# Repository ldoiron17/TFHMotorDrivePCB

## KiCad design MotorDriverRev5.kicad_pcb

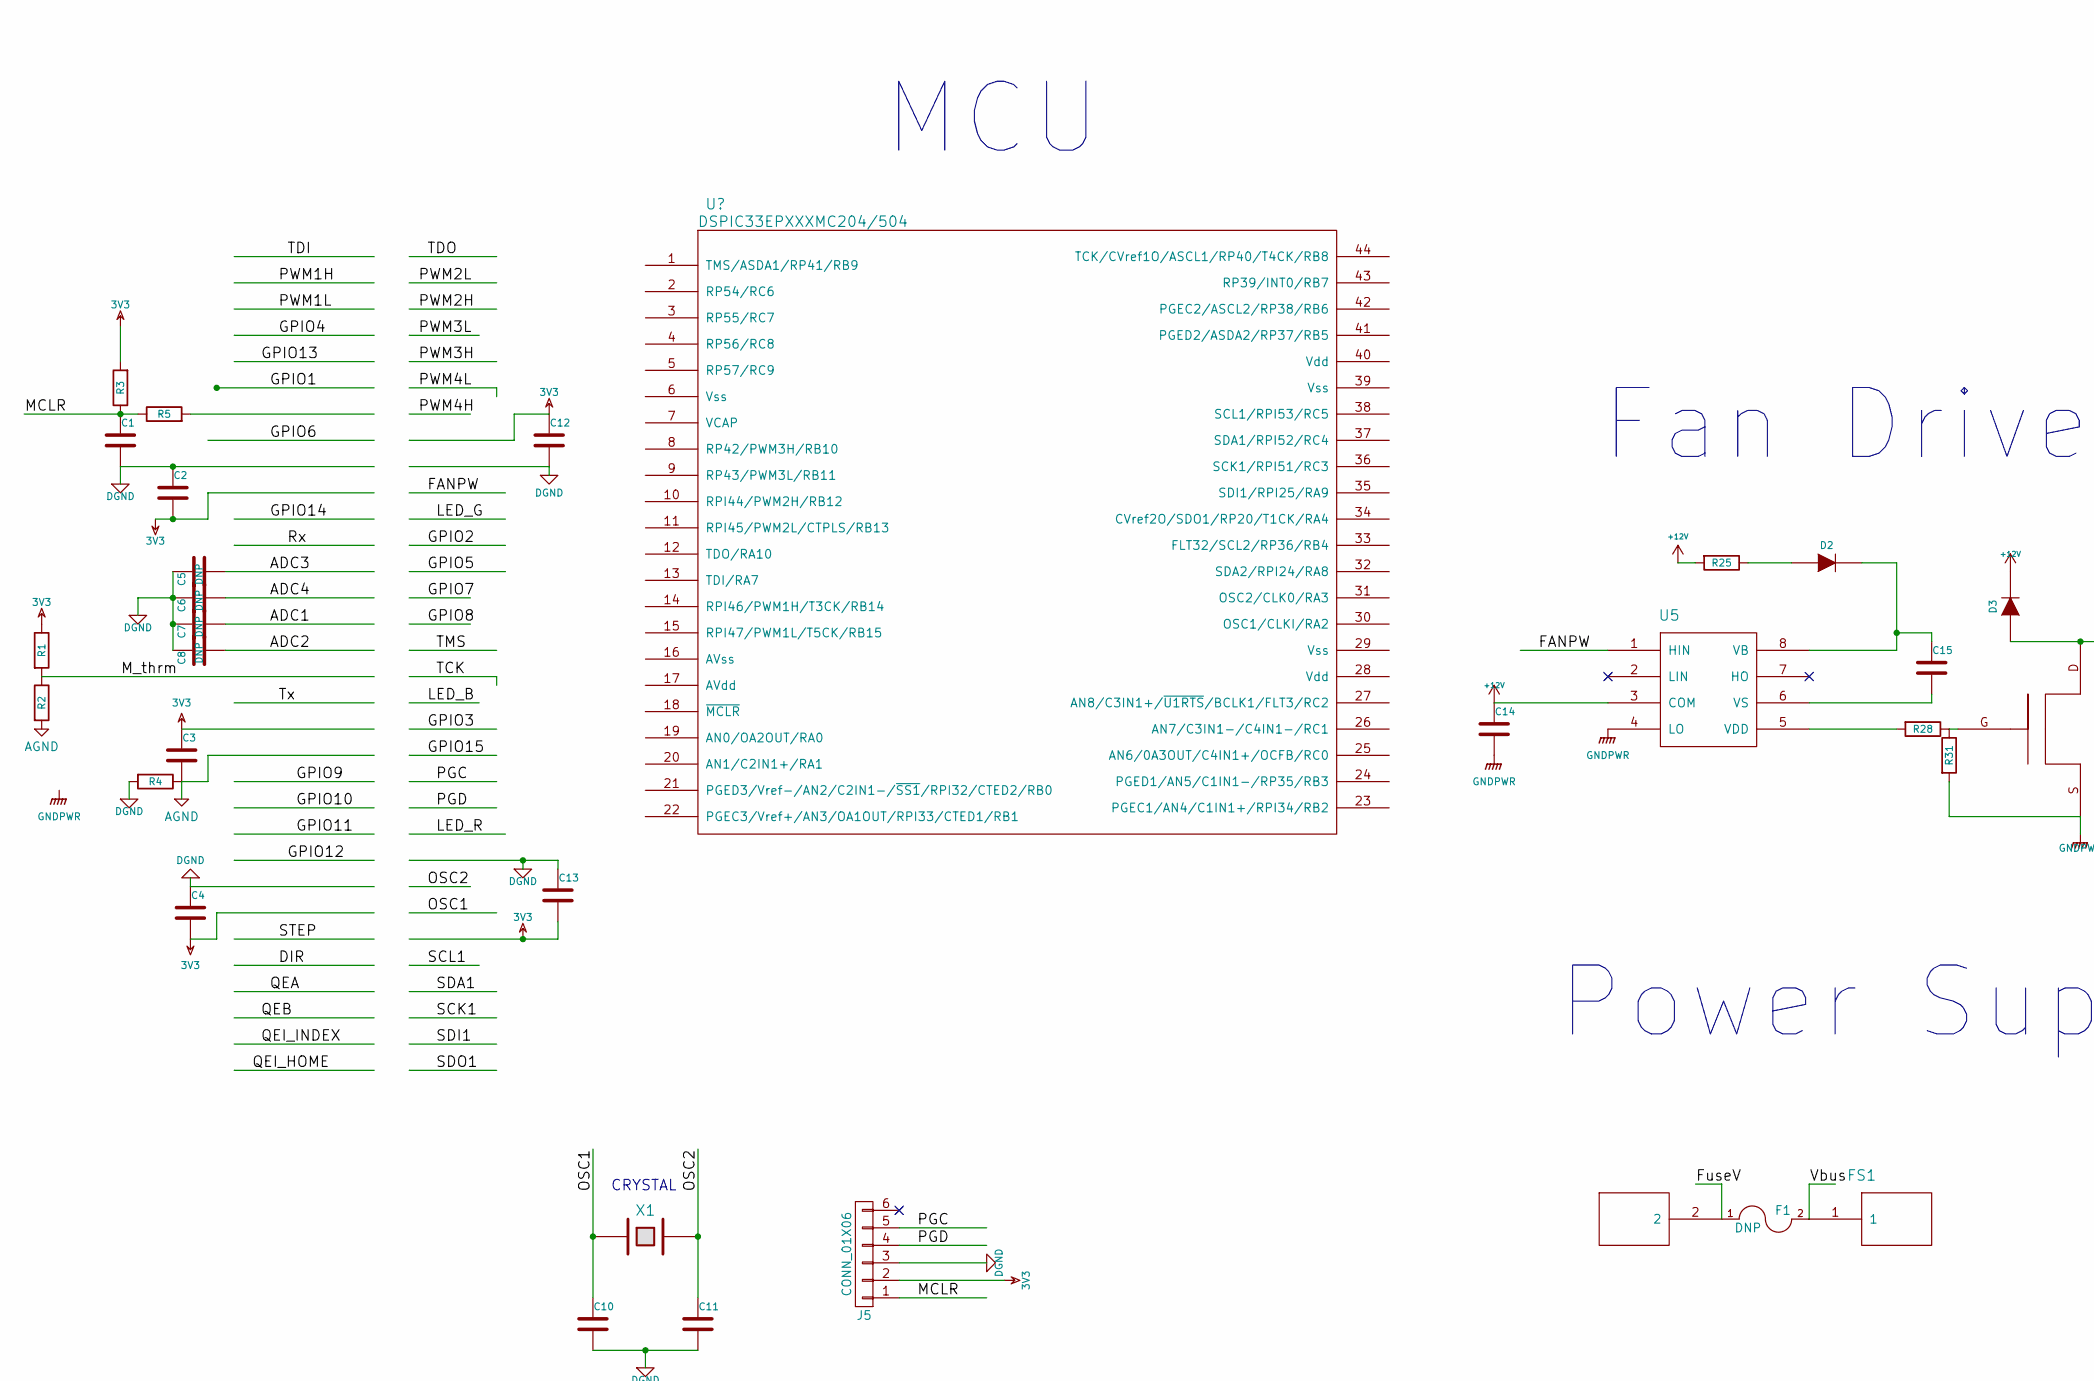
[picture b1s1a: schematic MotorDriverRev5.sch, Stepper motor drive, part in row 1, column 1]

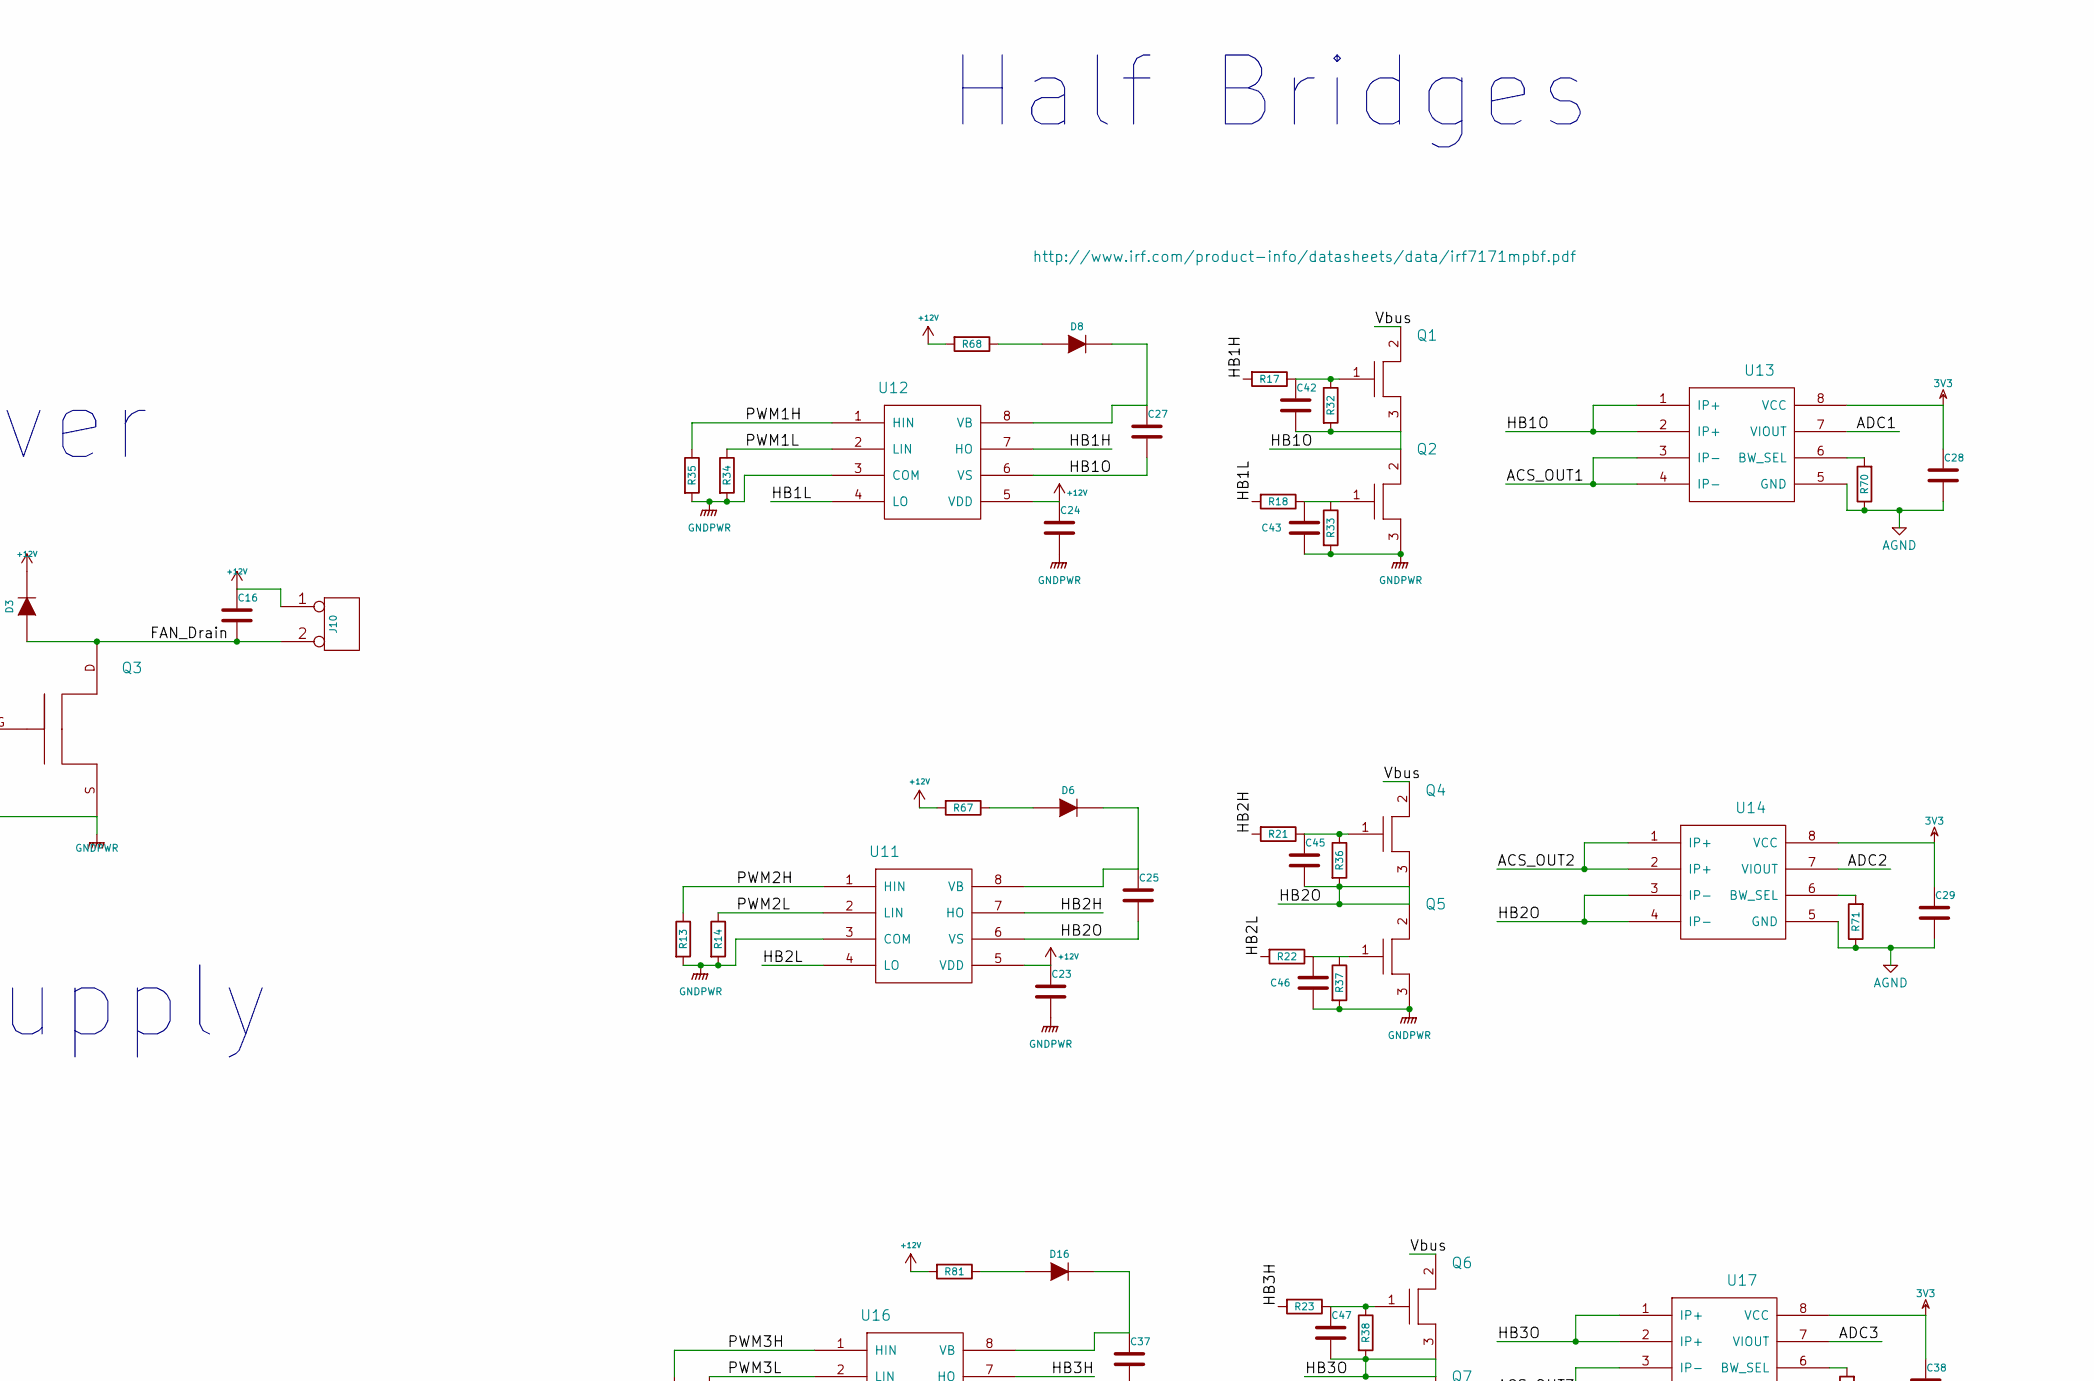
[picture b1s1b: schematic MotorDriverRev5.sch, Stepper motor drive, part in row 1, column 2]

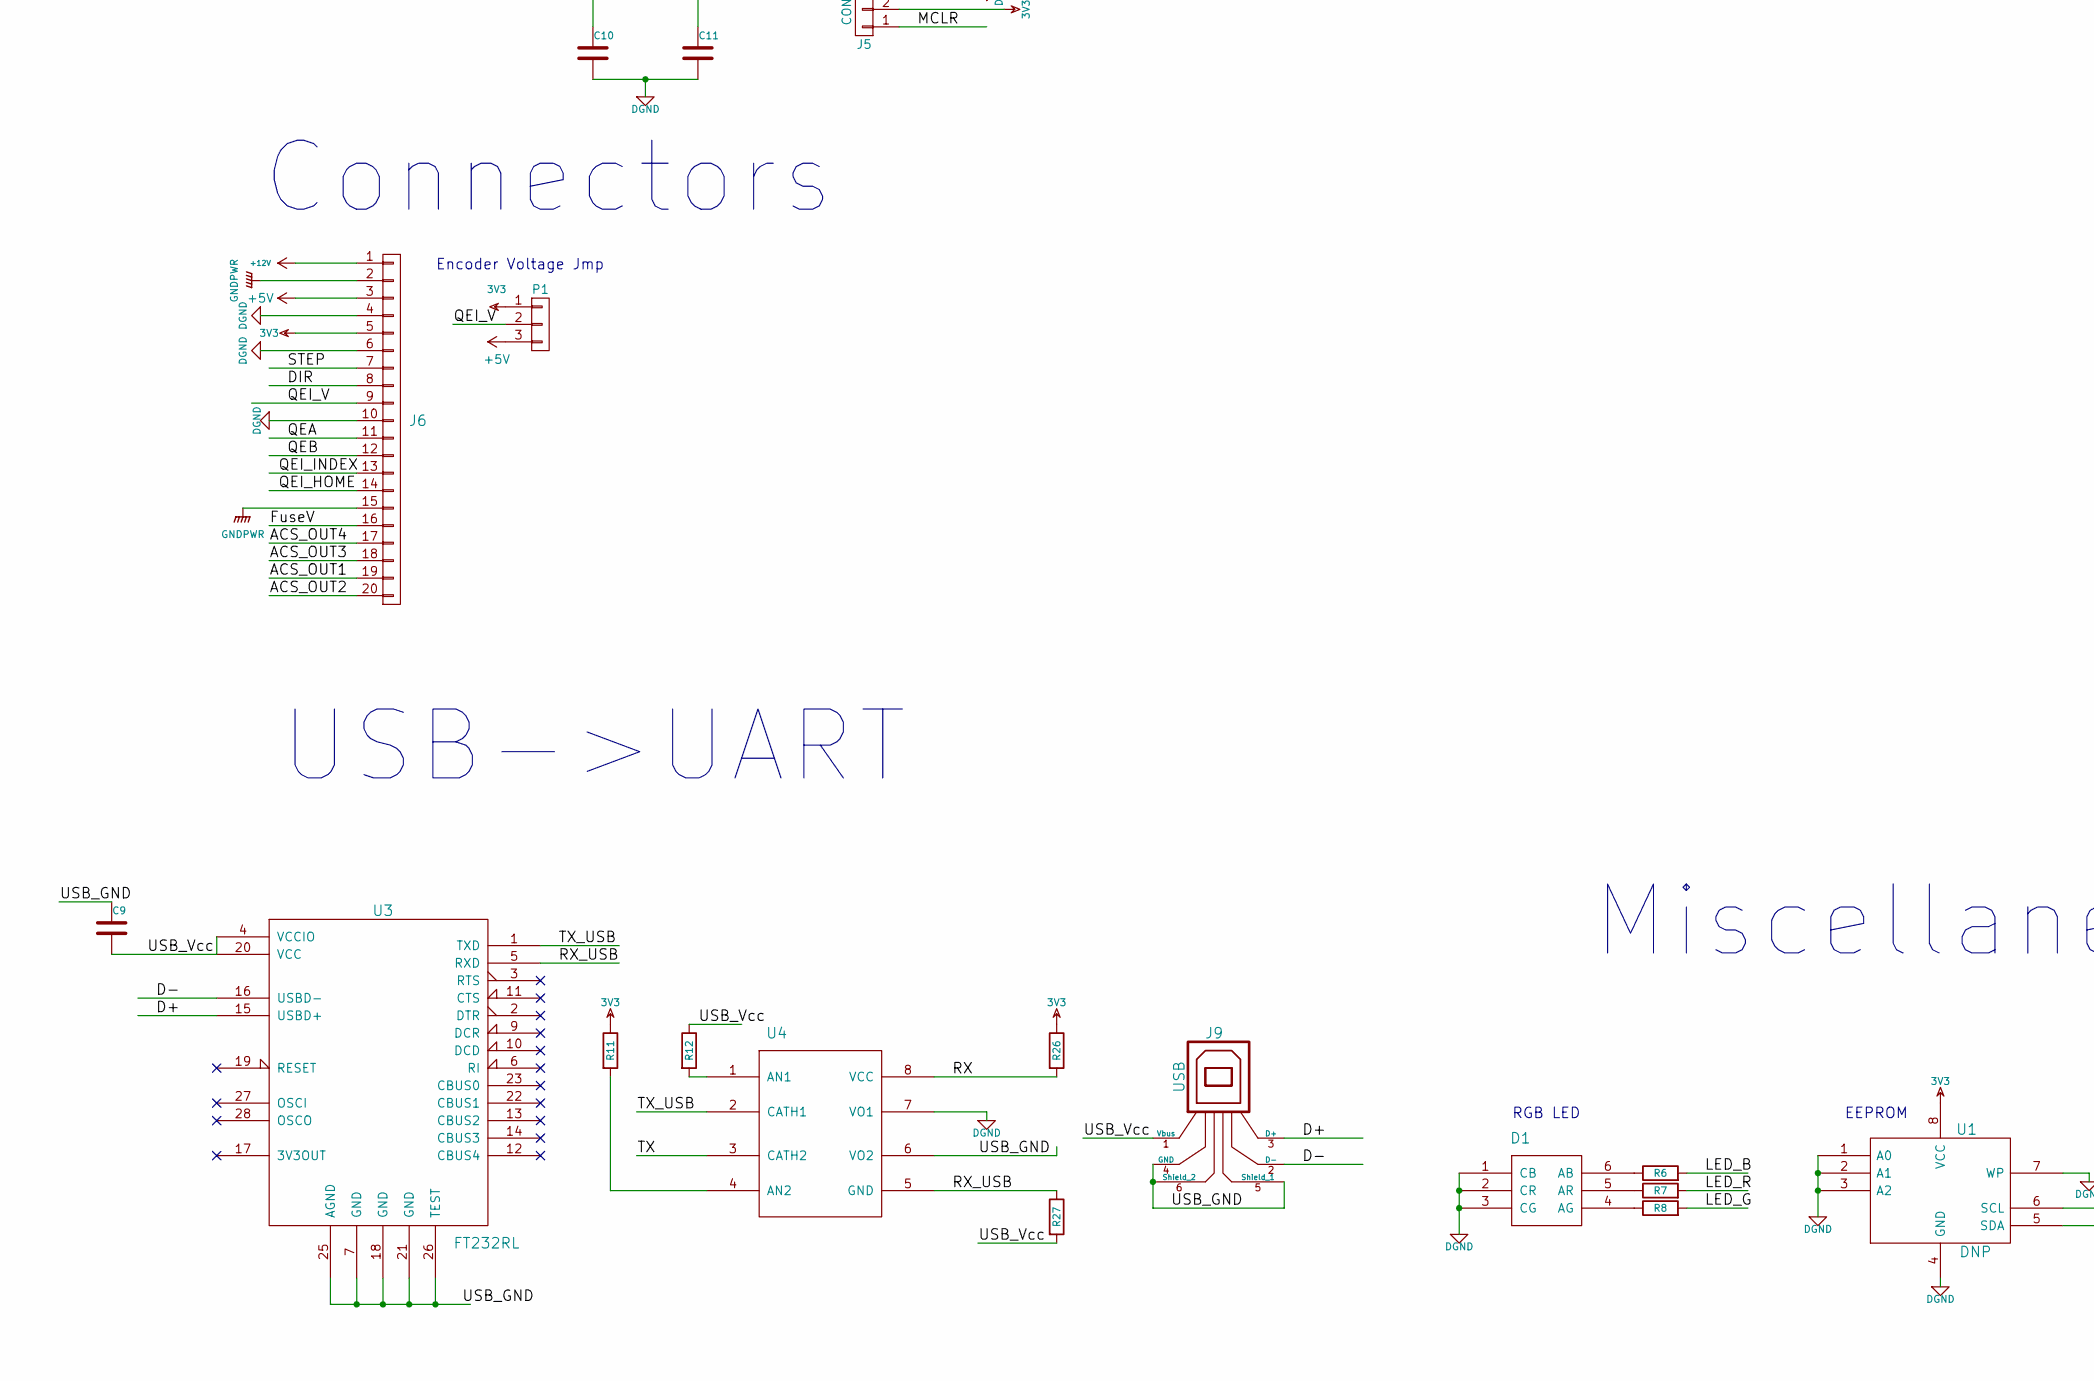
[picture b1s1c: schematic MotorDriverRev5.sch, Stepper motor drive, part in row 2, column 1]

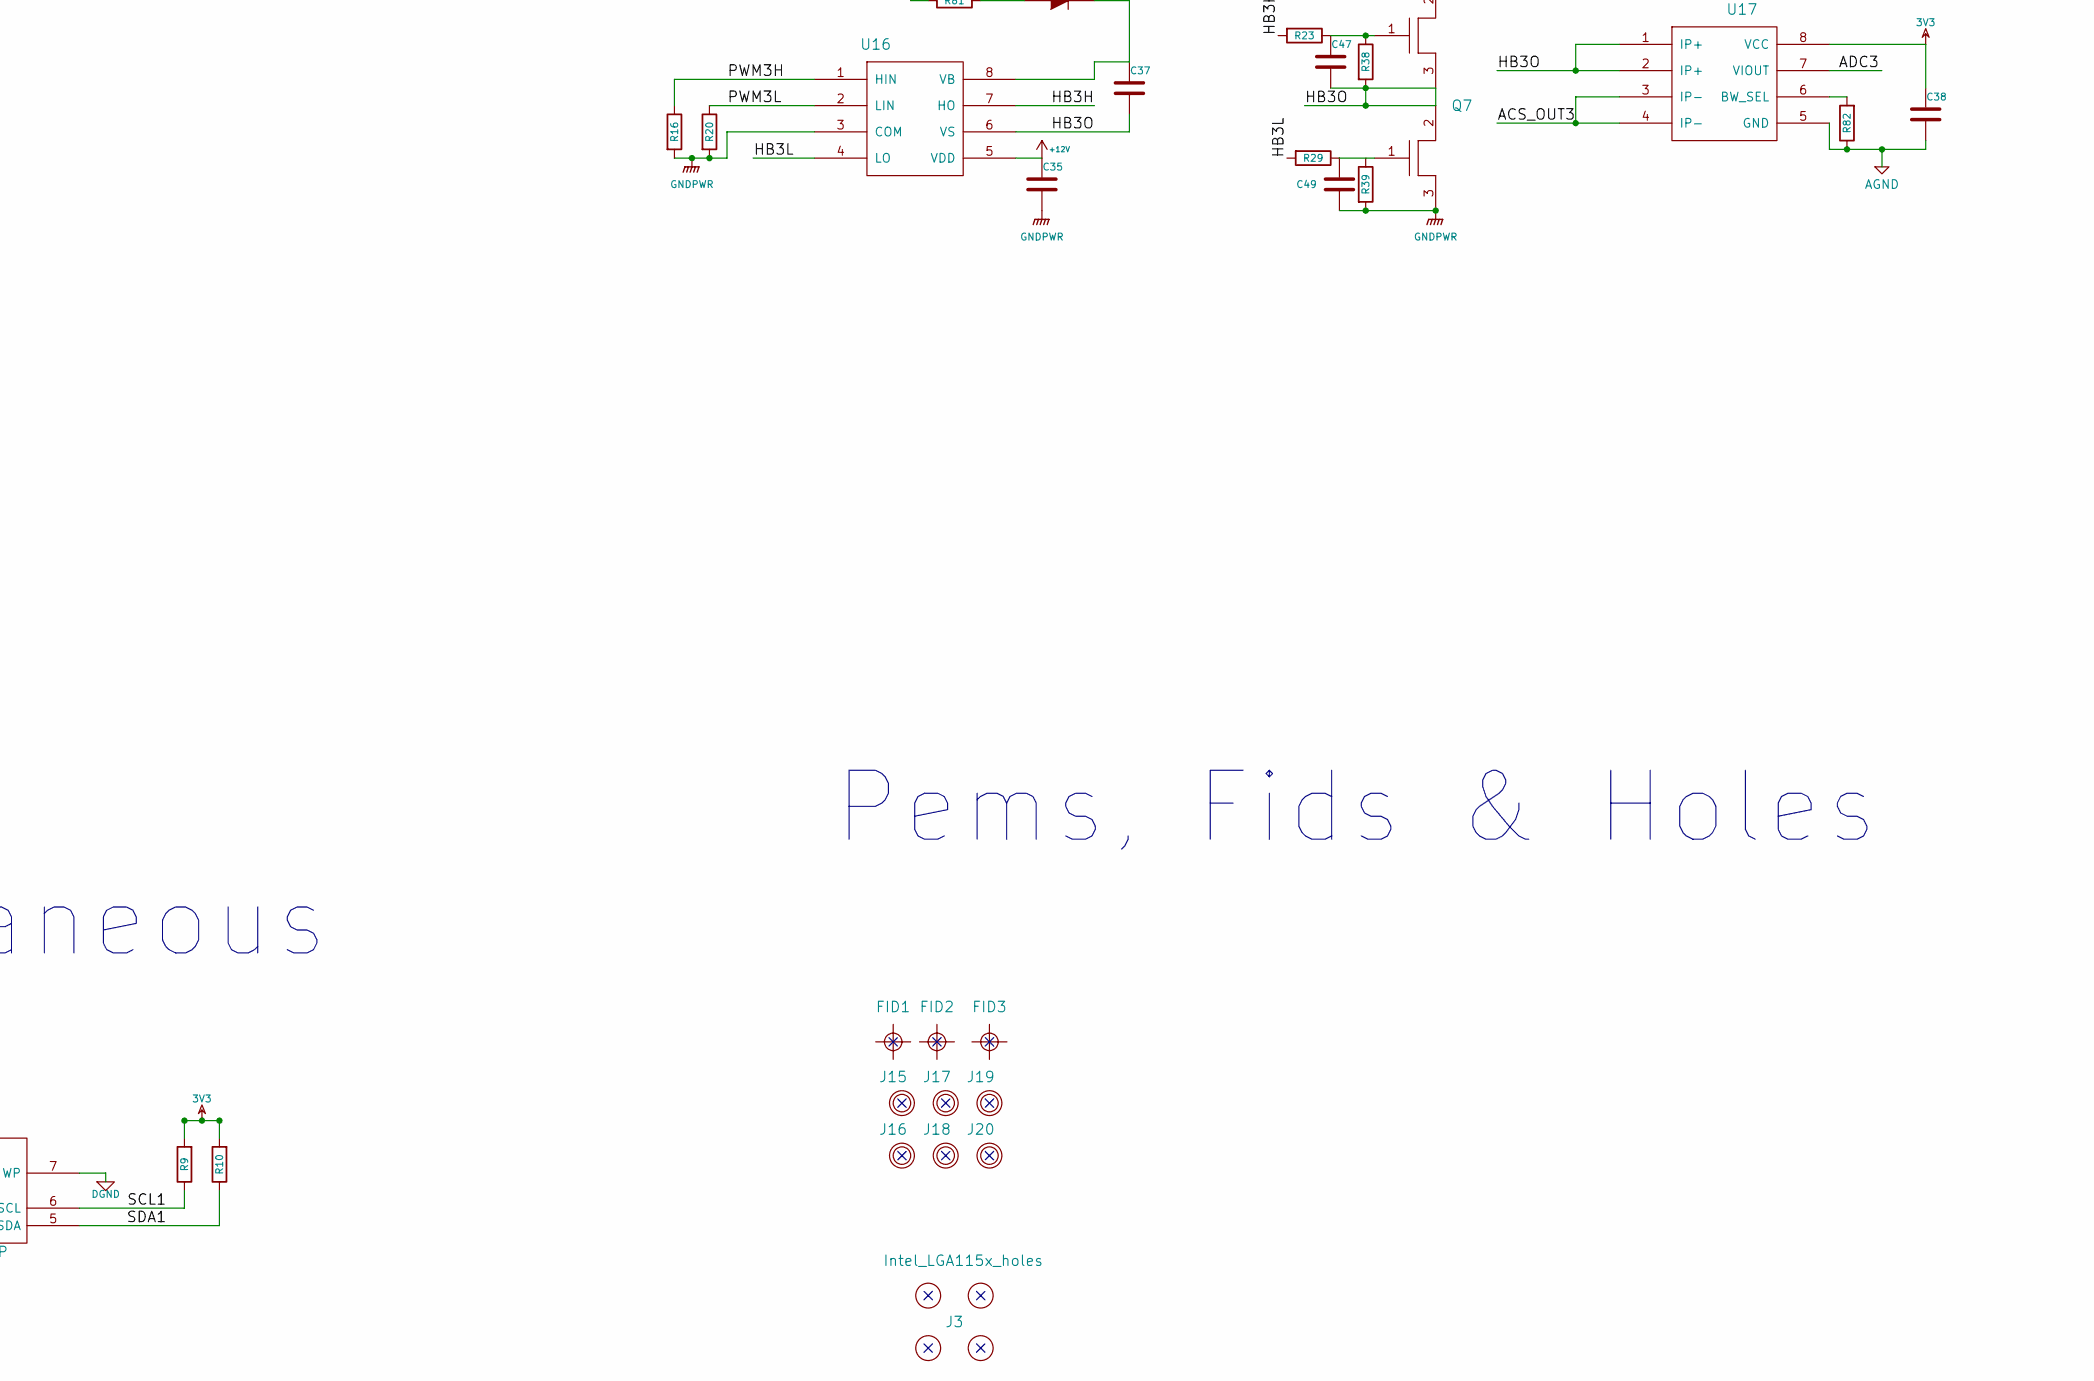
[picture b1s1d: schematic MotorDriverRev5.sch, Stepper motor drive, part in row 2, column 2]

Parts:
C1, C2, C3, C4, C23, C24, C25, C27, C28, C29, C35, C37, C38: 100nF. 0805, X7R 25V; C_0603; MFG Part # N/A
C5, C6, C7, C8: DNP; C_0603; MFG Part # N/A
C9, C16: 10uF. 0805, X7R 25V; C_0805; MFG Part # N/A
C10, C11: 22pF. 0805, X7R 25V; C_0603; MFG Part # N/A
C12, C13: 100nF. 0603, X7R 25V; C_0603; MFG Part # N/A
C14: 100nF. 0603, X7R 25V; R_0603; MFG Part # N/A
C15: DNP; R_0603; MFG Part # N/A
C42, C43, C45, C46, C47, C49: 1nF. 0603, X7R 25V; C_0603; MFG Part # N/A
D1: RGB_LED_6PLCC; LED_RGB_PLLC-6; MFG Part # LTRBGFSF-ABCB-QKYO-Z
D2: DNP; SOD-323; MFG Part # BAS21AHT1G
D3: Diode; SMB; MFG Part # STTH1R06U
D6, D8, D16: Diode; SOD-323; MFG Part # BAS21AHT1G
F1: DNP; MFG Part # 0477016.MXP
FID1: Fiducial; Fiducial_classic_big_CopperTop_Type1_RevC; MFG Part # N/A
FID2, FID3: Fiducial; Fiducial_classic_big_CopperTop_Type1_RevC
FS1: Fuse_Holder_5mmX20mm; Fuse_holder_3512_x2; MFG Part # 3512
J3: Intel_LGA115x_holes
J5: CONN_01X06; Pin_Header_Straight_1x06; MFG Part # N/A
J6: N/A; TERM_BLOCK_5.08MM_VERT_20POS; MFG Part # OSTTC102162
J9: USB; USB_B; MFG Part # 8144-B02022-L
J10: n/a; fan_60mmx60mmx25mm
J15, J16, J17, J18, J19, J20: Board_hole; BRD_HOLE; MFG Part # N/A
P1: DNP; Pin_Header_Straight_1x03; MFG Part # N/A
Q1: FET_small; IR-directFET_MN-Outline_Names; MFG Part # IRF6662TRPBF
Q2, Q4, Q5, Q6, Q7: FET_small; DirectFETMZ; MFG Part # IRF6662TRPBF
Q3: FET; DPAKGDS; MFG Part # FDD6N25TM
R1, R3, R5, R11, R12, R13, R14, R16, R20, R26, R27, R31, R32, R33, R34, R35, R36, R37, R38, R39: 10k, 0603 1%; R_0603; MFG Part # N/A
R2: N/A; R_0603; MFG Part # NCP18XH103F03RB
R4, R70, R71, R82: 0R, 0603 1%; R_0603; MFG Part # N/A
R6, R7, R8: 1k, 0603 1%; R_0603; MFG Part # N/A
R9, R10: DNP; R_0603; MFG Part # 1k, 0603 1%
R17, R18, R21, R22, R23, R28, R29, R67, R68, R81: 2R2, 0805 1%, 1/8W; R_0805; MFG Part # MCR10ERTFL2R20
R25: DNP; R_0805; MFG Part # MCR10ERTFL2R20
U1: DNP; SOIC-8-N; MFG Part # 24C16
U3: FT232RL; SSOP28; MFG Part # FT232RL
U4: Opto-2Channel; SMD8-2ChannelOpto; MFG Part # LTV-827S
U5, U11, U12, U16: FAN7190_F085; SOIC-8-N; MFG Part # FAN7190MX_F085
U13, U14, U17: Hall effect; SOIC-8-N; MFG Part # ACS725LLCTR-20AB-T
X1: CRYSTAL; TXC_XTAL_SMD; MFG Part # 7A-8.000MAAE-T

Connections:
3V3: C2.2, C3.1, C4.2, C12.1, C13.2, C28.1, C29.1, C38.1, J5.2, J6.5, P1.1, R1.1, R3.2, R9.2, R10.2, R11.1, R26.1, U1.8 (VCC), U13.8 (VCC), U14.8 (VCC), U17.8 (VCC); also elsewhere on the board
+5V: J6.3, P1.3
+12V: C14.1, C16.1, C23.1, C24.1, C35.1, D3.2 (K), J6.1, J10.1, R25.2, R67.2, R68.2, R81.2, U5.3 (COM), U11.5 (VDD), U12.5 (VDD), U16.5 (VDD)
/ACS_OUT1: J6.19, U13.3 (IP-), U13.4 (IP-)
/ACS_OUT2: J6.20, U14.1 (IP+), U14.2 (IP+)
/ACS_OUT3: J6.18, U17.3 (IP-), U17.4 (IP-)
/ACS_OUT4: J6.17
/ADC1: C7.1, U13.7 (VIOUT); also elsewhere on the board
/ADC2: C8.1, U14.7 (VIOUT); also elsewhere on the board
/ADC3: C5.1, U17.7 (VIOUT); also elsewhere on the board
/ADC4: C6.1; also elsewhere on the board
/D+: J9.3 (D+), U3.15 (USBD+)
/D-: J9.2 (D-), U3.16 (USBD-)
/DIR: J6.8; also elsewhere on the board
/FANPW: U5.1 (HIN); also elsewhere on the board
/FAN_Drain: C16.2, D3.1 (A), J10.2 (PM), Q3.D
/FuseV: F1.1, FS1.2, J6.16
/HB1H: R17.2, U12.7 (HO)
/HB1L: R18.2, U12.4 (LO)
/HB1O: C27.2, C42.2, Q1.3, Q2.2, R32.2, U12.6 (VS), U13.1 (IP+), U13.2 (IP+)
/HB2H: R21.2, U11.7 (HO)
/HB2L: R22.2, U11.4 (LO)
/HB2O: C25.2, C45.2, Q4.3, Q5.2, R36.2, U11.6 (VS), U14.3 (IP-), U14.4 (IP-)
/HB3H: R23.2, U16.7 (HO)
/HB3L: R29.2, U16.4 (LO)
/HB3O: C37.2, C47.2, Q6.3, Q7.2, R38.2, U16.6 (VS), U17.1 (IP+), U17.2 (IP+)
/LED_B: R6.2; also elsewhere on the board
/LED_G: R8.2; also elsewhere on the board
/LED_R: R7.2; also elsewhere on the board
/MCLR: C1.1, J5.1, R3.1, R5.1
/M_thrm: R1.2, R2.1; also elsewhere on the board
/OSC1: C10.1, X1.1; also elsewhere on the board
/OSC2: C11.1, X1.2; also elsewhere on the board
/PGC: J5.5; also elsewhere on the board
/PGD: J5.4; also elsewhere on the board
/PWM1H: R35.1, U12.1 (HIN); also elsewhere on the board
/PWM1L: R34.1, U12.2 (LIN); also elsewhere on the board
/PWM2H: R13.1, U11.1 (HIN); also elsewhere on the board
/PWM2L: R14.1, U11.2 (LIN); also elsewhere on the board
/PWM3H: R16.1, U16.1 (HIN); also elsewhere on the board
/PWM3L: R20.1, U16.2 (LIN); also elsewhere on the board
/QEA: J6.11; also elsewhere on the board
/QEB: J6.12; also elsewhere on the board
/QEI_HOME: J6.14; also elsewhere on the board
/QEI_INDEX: J6.13; also elsewhere on the board
/QEI_V: J6.9, P1.2
/RX: R26.2, U4.8 (VCC); also elsewhere on the board
/RX_USB: R27.1, U3.5 (RXD), U4.5 (GND)
/SCL1: R9.1, U1.6 (SCL); also elsewhere on the board
/SDA1: R10.1, U1.5 (SDA); also elsewhere on the board
/STEP: J6.7; also elsewhere on the board
/TX: U4.3 (CATH2); also elsewhere on the board
/TX_USB: U3.1 (TXD), U4.2 (CATH1)
/USB_GND: C9.1, J9.4 (GND), J9.5 (Shield_1), J9.6 (Shield_2), U3.7 (GND), U3.18 (GND), U3.21 (GND), U3.25 (AGND), U3.26 (TEST), U4.6 (VO2)
/USB_Vcc: C9.2, J9.1 (Vbus), R12.1, R27.2, U3.4 (VCCIO), U3.20 (VCC)
/Vbus: F1.2, FS1.1, Q1.2, Q4.2, Q6.2
AGND: C3.2, C28.2, C29.2, C38.2, R2.2, R4.1, R70.1, R71.1, R82.1, U13.5 (GND), U14.5 (GND), U17.5 (GND); also elsewhere on the board
DGND: C1.2, C2.1, C4.1, C5.2, C6.2, C7.2, C8.2, C10.2, C11.2, C12.2, C13.1, D1.1 (CB), D1.2 (CR), D1.3 (CG), J5.3, J6.4, J6.6, J6.10, R4.2, U1.1 (A0), U1.2 (A1), U1.3 (A2), U1.4 (GND), U1.7 (WP), U4.7 (VO1); also elsewhere on the board
GNDPWR: C14.2, C23.2, C24.2, C35.2, C43.2, C46.2, C49.2, J6.2, J6.15, Q2.3, Q3.S, Q5.3, Q7.3, R13.2, R14.2, R16.2, R20.2, R31.2, R33.2, R34.2, R35.2, R37.2, R39.2, U5.4 (LO), U11.3 (COM), U12.3 (COM), U16.3 (COM)
unnamed: C15.1, D2.2 (K), U5.8 (VB)
unnamed: C15.2, U5.6 (VS)
unnamed: C25.1, D6.2 (K), U11.8 (VB)
unnamed: C27.1, D8.2 (K), U12.8 (VB)
unnamed: C37.1, D16.2 (K), U16.8 (VB)
unnamed: C42.1, Q1.1, R17.1, R32.1
unnamed: C43.1, Q2.1, R18.1
unnamed: C45.1, Q4.1, R21.1, R36.1
unnamed: C46.1, Q5.1, R22.1
unnamed: C47.1, Q6.1, R23.1, R38.1
unnamed: C49.1, Q7.1, R29.1
unnamed: D1.4 (AG), R8.1
unnamed: D1.5 (AR), R7.1
unnamed: D1.6 (AB), R6.1
unnamed: D2.1 (A), R25.1
unnamed: D6.1 (A), R67.1
unnamed: D8.1 (A), R68.1
unnamed: D16.1 (A), R81.1
unnamed: Q3.G, R28.1, R31.1
unnamed 107: R5.2; also elsewhere on the board
unnamed: R11.2, U4.4 (AN2)
unnamed: R12.2, U4.1 (AN1)
unnamed: R28.2, U5.5 (VDD)
unnamed: R70.2, U13.6 (BW_SEL)
unnamed: R71.2, U14.6 (BW_SEL)
unnamed: R82.2, U17.6 (BW_SEL)

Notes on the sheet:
MCU
Connectors
Power Supply
Pems, Fids & Holes
Miscellaneous
USB->UART
Fan Driver
Encoder Voltage Jmp
Half Bridges
RGB LED
EEPROM
CRYSTAL

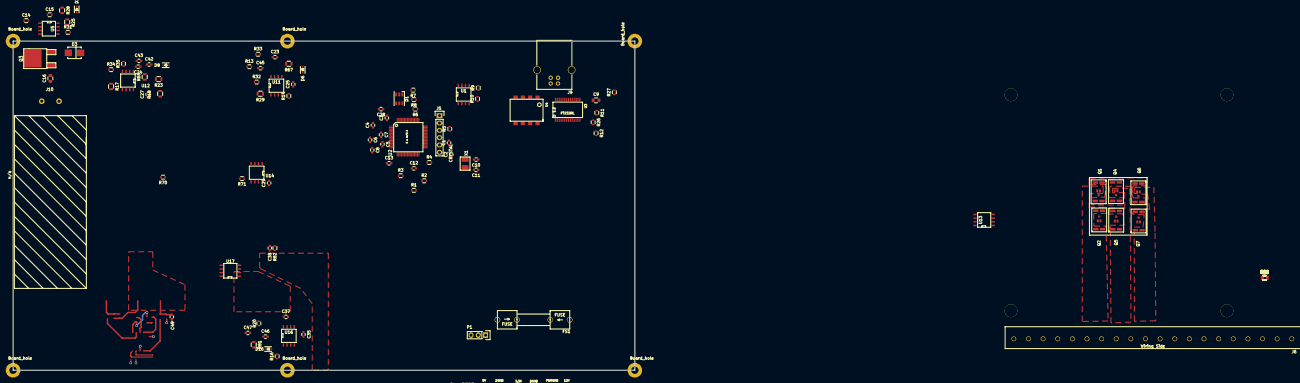
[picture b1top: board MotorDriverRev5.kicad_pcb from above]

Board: 4 copper layers, 215.9 x 114.3 mm, 113 parts (0 on the bottom side), 84 nets.

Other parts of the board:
U2: mcu; TQFP_64

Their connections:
3V3: U2.10, U2.19, U2.26, U2.38, U2.57; also elsewhere on the board
/ADC1: U2.15; also elsewhere on the board
/ADC2: U2.16; also elsewhere on the board
/ADC3: U2.13; also elsewhere on the board
/ADC4: U2.14; also elsewhere on the board
/DIR: U2.28; also elsewhere on the board
/FANPW: U2.55; also elsewhere on the board
/LED_B: U2.47; also elsewhere on the board
/LED_G: U2.54; also elsewhere on the board
/LED_R: U2.42; also elsewhere on the board
/M_thrm: U2.17; also elsewhere on the board
/OSC1: U2.39; also elsewhere on the board
/OSC2: U2.40; also elsewhere on the board
/PGC: U2.44; also elsewhere on the board
/PGD: U2.43; also elsewhere on the board
/PWM1H: U2.2; also elsewhere on the board
/PWM1L: U2.3; also elsewhere on the board
/PWM2H: U2.62; also elsewhere on the board
/PWM2L: U2.63; also elsewhere on the board
/PWM3H: U2.60; also elsewhere on the board
/PWM3L: U2.61; also elsewhere on the board
/QEA: U2.29; also elsewhere on the board
/QEB: U2.30; also elsewhere on the board
/QEI_HOME: U2.32; also elsewhere on the board
/QEI_INDEX: U2.31; also elsewhere on the board
/RX: U2.12; also elsewhere on the board
/SCL1: U2.37; also elsewhere on the board
/SDA1: U2.36; also elsewhere on the board
/STEP: U2.27; also elsewhere on the board
/TX: U2.18; also elsewhere on the board
AGND: U2.20; also elsewhere on the board
DGND: U2.9, U2.25, U2.41, U2.56; also elsewhere on the board
unnamed 107: U2.7; also elsewhere on the board

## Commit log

2016-03-13 :tada: Added .gitattributes & .gitignore files
2016-03-13 test
    testing github
2016-03-13 Deleted old file paths for sch libs
2016-03-13 Updated libraries for using git
2016-03-14 began buck converter (test)
    added a mosfet, diode, and inductor underneath the power supply portion
    of the schematic
